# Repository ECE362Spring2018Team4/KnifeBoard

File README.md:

# KnifeBoard
Board to be mounted on knife

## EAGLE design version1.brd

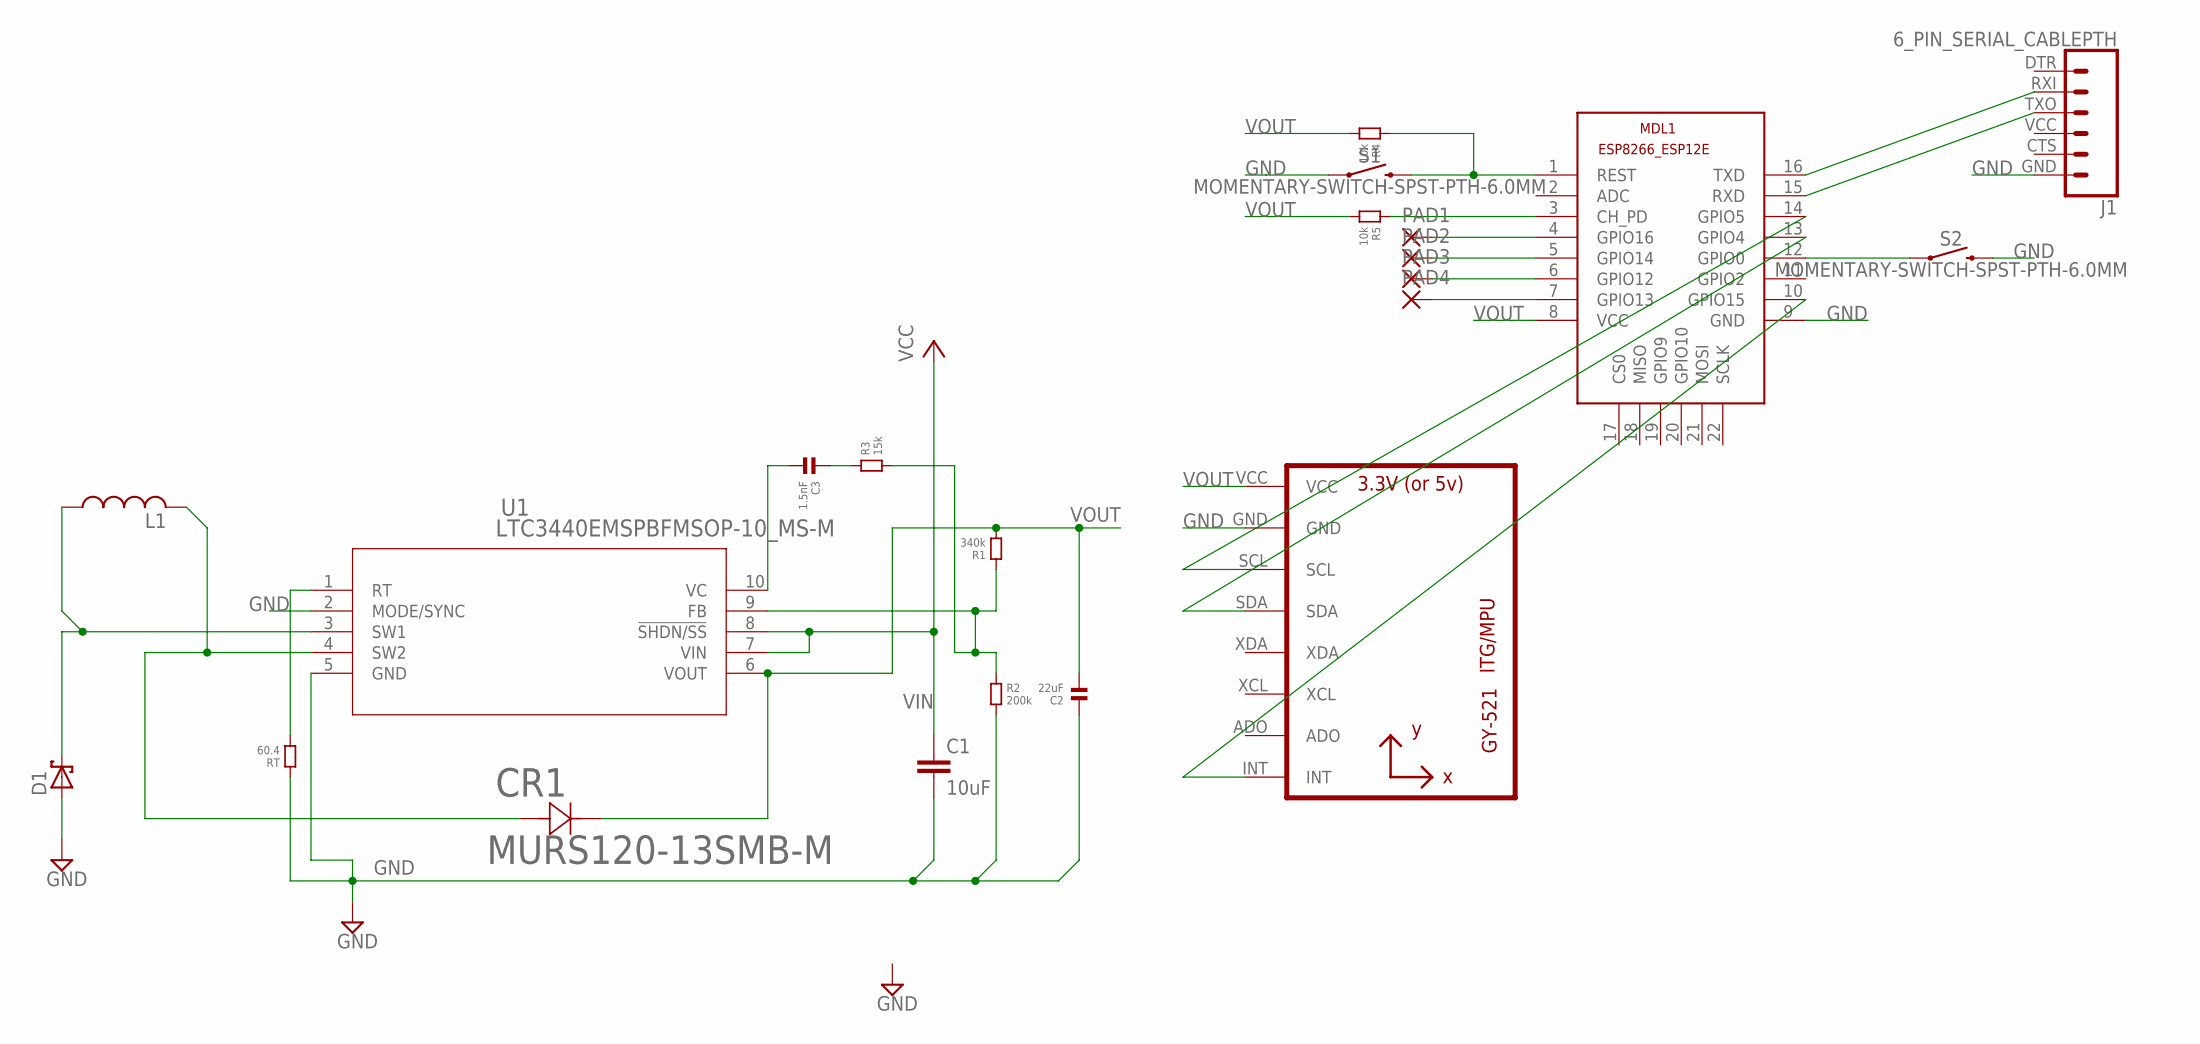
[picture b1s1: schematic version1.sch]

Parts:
C1: 10uF; 1206
C2: 22uF; 1206
C3: 1.5nF; 1206
CR1: MURS120-13SMB-M; SMB-M
D1: SCHOTTKY-DIODEDFLS130L-7; POWERDI-123
J1: 6_PIN_SERIAL_CABLEPTH; FTDI_BASIC
L1: INDUCTOR-SUMIDA-CDRH4D18
MDL1: ESP8266-12EESP8266-ESP12E; ESP8266-ESP12E
PAD1, PAD2, PAD3, PAD4: 1,6/0,9
R1: 340k; 1206
R2: 200k; 1206
R3: 15k; 1206
R4, R5: 10k; 1206
RT: 60.4; 1206
S1, S2: MOMENTARY-SWITCH-SPST-PTH-6.0MM; TACTILE_SWITCH_PTH_6.0MM
U1: LTC3440EMSPBFMSOP-10_MS-M; MSOP-10_MS-M
U2: GY-521MPU6050; GY-521

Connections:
GND: C1.2, C2.1, D1.A, J1.GND (6), MDL1.9 (GND), R2.2, RT.1, S1.1, S2.3 (2), U1.2 (MODE/SYNC), U1.5 (GND), U2.GND
unnamed: D1.C, L1.P$1, U1.3 (SW1)
unnamed: CR1.2 (21), L1.P$2, U1.4 (SW2)
unnamed: C3.2, U1.10 (VC)
unnamed: RT.2, U1.1 (RT)
unnamed: C3.1, R3.1
unnamed: R1.1, R2.1, R3.2, U1.9 (FB)
unnamed: MDL1.12 (GPIO0), S2.1
unnamed: MDL1.1 (REST), R4.1, S1.3 (2)
unnamed: J1.RXI (2), MDL1.16 (TXD)
unnamed: MDL1.3 (CH_PD), R5.1
unnamed: MDL1.14 (GPIO5), U2.SCL
unnamed: MDL1.13 (GPIO4), U2.SDA
unnamed: MDL1.10 (GPIO15), U2.INT
unnamed: J1.TXO (3), MDL1.15 (RXD)
unnamed: MDL1.4 (GPIO16), PAD1.1
unnamed: MDL1.5 (GPIO14), PAD2.1
unnamed: MDL1.6 (GPIO12), PAD3.1
unnamed: MDL1.7 (GPIO13), PAD4.1
VIN: C1.1, U1.7 (VIN), U1.8 (!SHDN/SS)
VOUT: C2.2, CR1.1 (12), MDL1.8 (VCC), R1.2, R4.2, R5.2, U1.6 (VOUT), U2.VCC

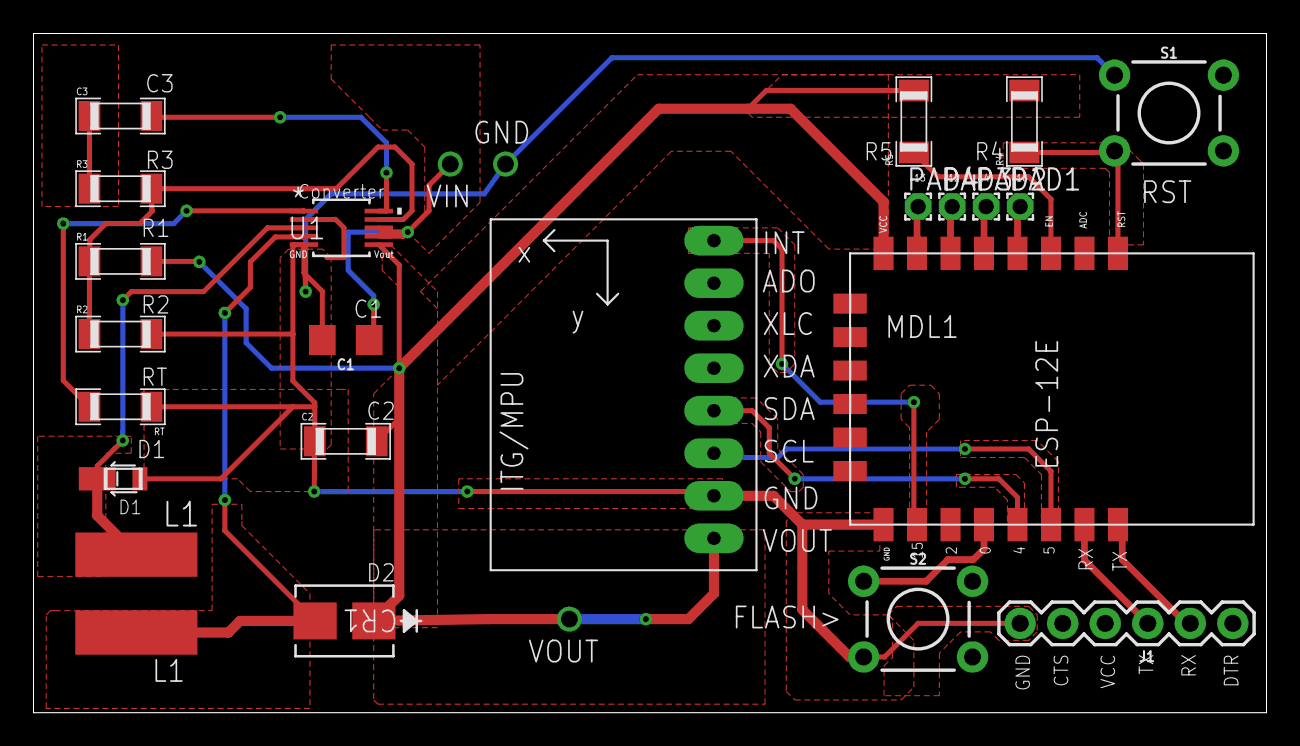
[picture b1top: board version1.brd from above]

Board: 2 copper layers, 73.6 x 40.6 mm, 22 parts (0 on the bottom side), 21 nets.

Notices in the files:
parts and their libraries:
SparkFun-Capacitors: Licensing: Creative Commons ShareAlike 4.0 International - https://creativecommons.org/licenses/by-sa/4.0
